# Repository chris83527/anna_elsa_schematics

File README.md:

# Schematics for Anna & Elsa fruit machine project
## based on ESP32 microcontroller

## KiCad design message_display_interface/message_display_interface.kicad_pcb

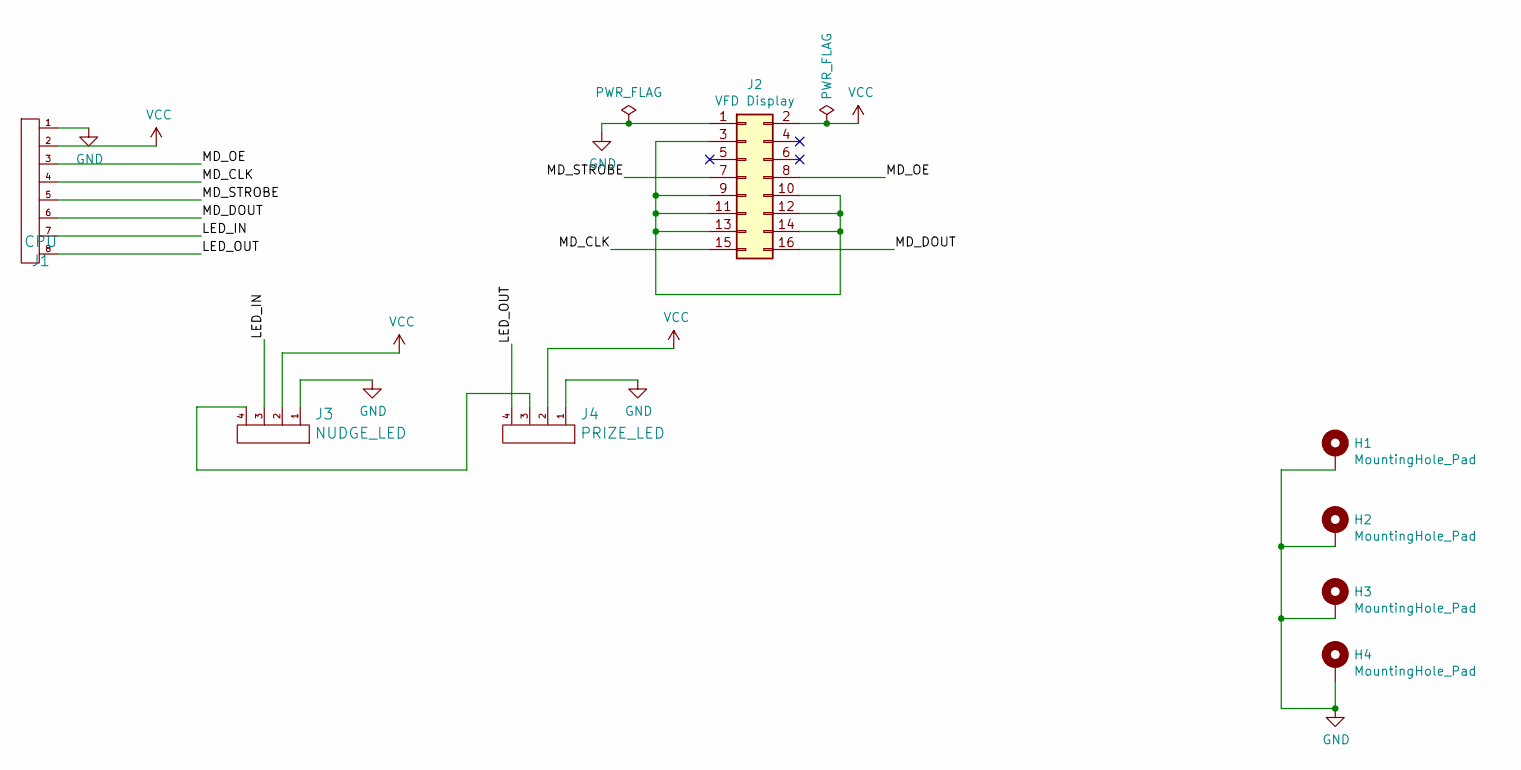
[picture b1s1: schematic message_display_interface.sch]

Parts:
H1, H2, H3, H4: MountingHole_Pad; MountingHole_3.2mm_M3_Pad
J1: CPU; JST_XH_B8B-XH-A_1x08_P2.50mm_Vertical
J2: VFD Display; IDC-Header_2x08_P2.54mm_Vertical
J3: NUDGE_LED; JST_XH_B4B-XH-A_1x04_P2.50mm_Vertical
J4: PRIZE_LED; JST_XH_B4B-XH-A_1x04_P2.50mm_Vertical

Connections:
/LED_IN: J1.7, J3.3
/LED_OUT: J1.8, J4.4
/MD_CLK: J1.4, J2.15
/MD_DOUT: J1.6, J2.16
/MD_OE: J1.3, J2.8
/MD_STROBE: J1.5, J2.7
GND: H1.1, H2.1, H3.1, H4.1, J1.1, J2.1, J3.1, J4.1
unnamed: J2.3, J2.9, J2.10, J2.11, J2.12, J2.13, J2.14
unnamed: J3.4, J4.3
VCC: J1.2, J2.2, J3.2, J4.2

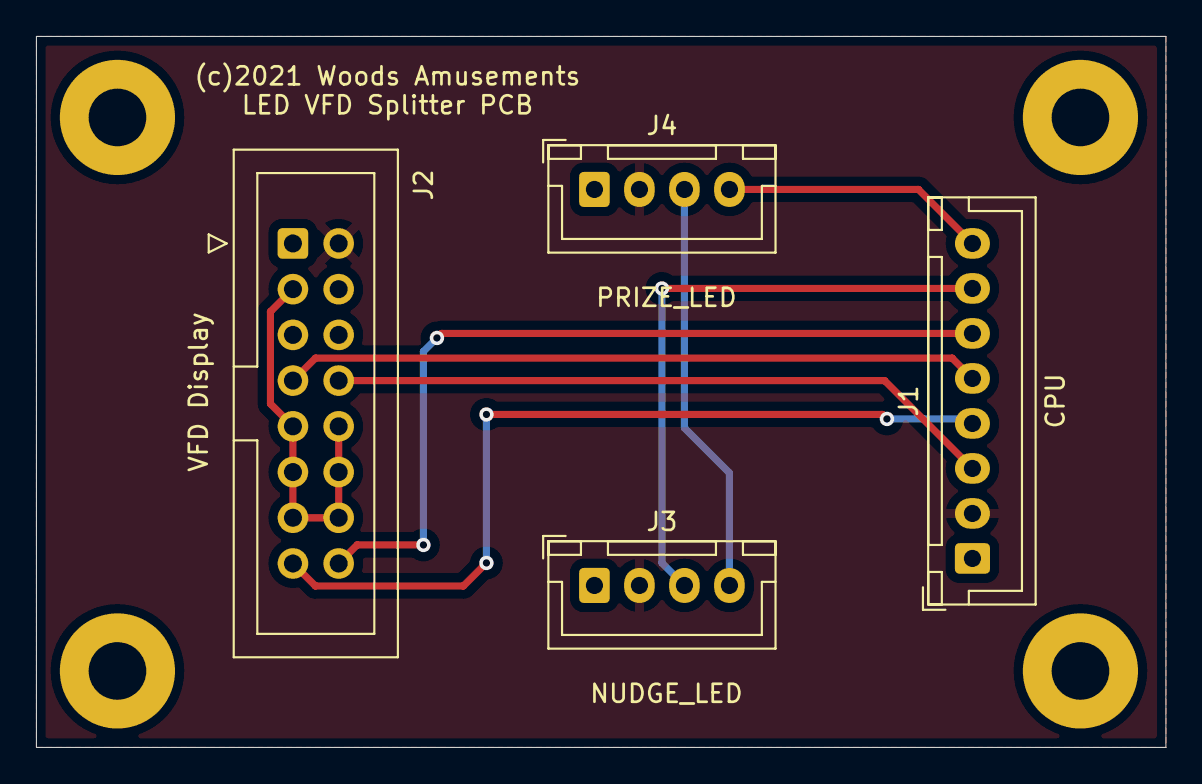
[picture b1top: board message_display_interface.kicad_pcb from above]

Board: 2 copper layers, 62.8 x 39.5 mm, 8 parts (0 on the bottom side), 10 nets.

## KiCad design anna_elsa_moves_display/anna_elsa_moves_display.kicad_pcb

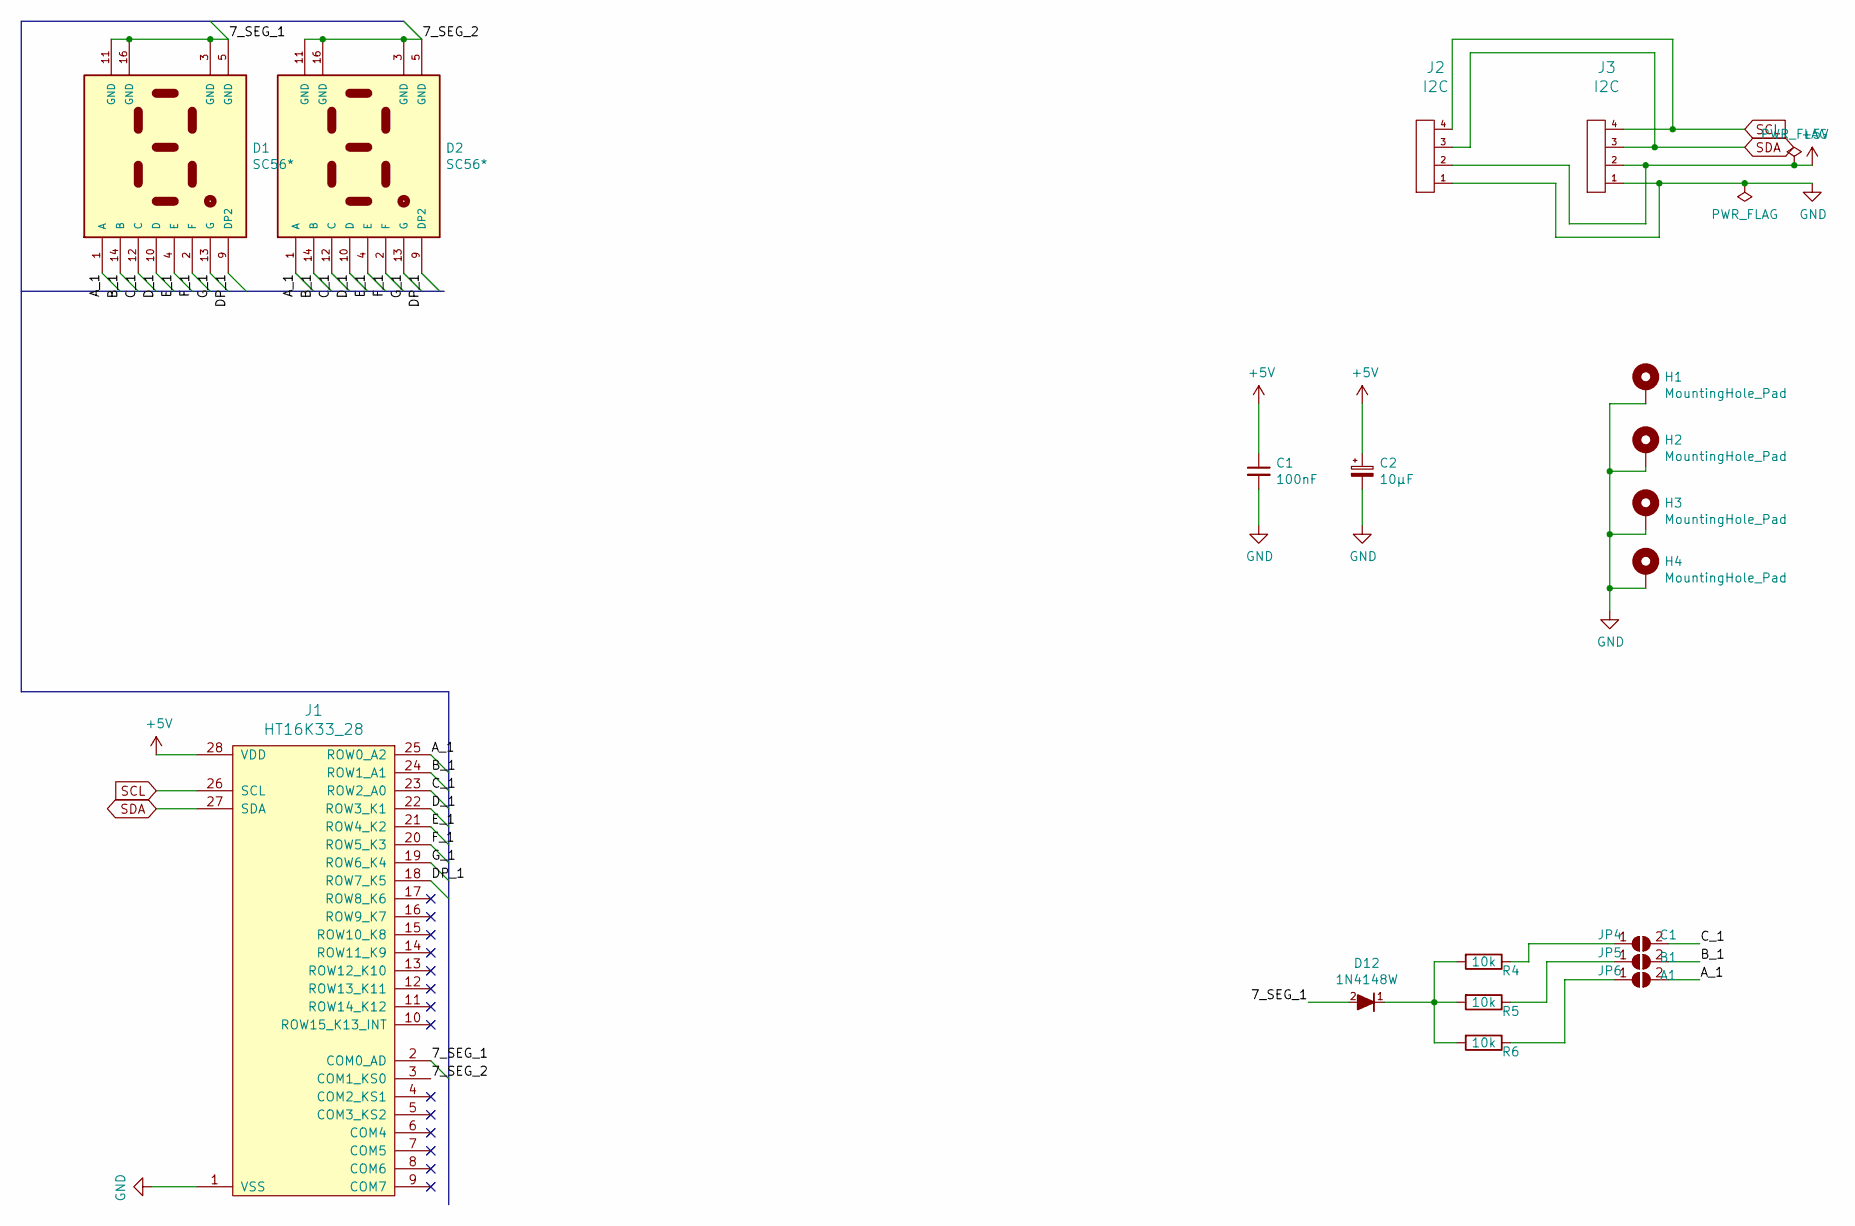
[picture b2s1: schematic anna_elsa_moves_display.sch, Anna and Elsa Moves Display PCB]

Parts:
C1: 100nF; C_Disc_D4.3mm_W1.9mm_P5.00mm; LCSC C14663
C2: 10µF; CP_Radial_D6.3mm_P2.50mm; LCSC C96123
D1, D2: SC56*; DIP14_KINGBRIGHT_SX08
D12: 1N4148W; D_A-405_P7.62mm_Horizontal; LCSC C81598
H1, H2, H3, H4: MountingHole_Pad; MountingHole_3.2mm_M3_Pad
J1: HT16K33_28; SOP-28_7.5x15.4mm_P1.27mm
J2, J3: I2C; JST_XH_B4B-XH-A_1x04_P2.50mm_Vertical
JP4: C1; SolderJumper-2_P1.3mm_Open_Pad1.0x1.5mm
JP5: B1; SolderJumper-2_P1.3mm_Open_Pad1.0x1.5mm
JP6: A1; SolderJumper-2_P1.3mm_Open_Pad1.0x1.5mm
R4, R6: 10k; R_Axial_DIN0207_L6.3mm_D2.5mm_P7.62mm_Horizontal; LCSC C25804
R5: 10k; R_Axial_DIN0207_L6.3mm_D2.5mm_P7.62mm_Horizontal

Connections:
+5V: C1.1, C2.1, J1.28 (VDD), J2.2, J3.2
/7_SEG_1: D1.3 (GND), D1.5 (GND), D1.11 (GND), D1.16 (GND), D12.2 (A), J1.2 (COM0_AD)
/7_SEG_2: D2.3 (GND), D2.5 (GND), D2.11 (GND), D2.16 (GND), J1.3 (COM1_KS0)
/A_1: D1.1 (A), D2.1 (A), J1.25 (ROW0_A2), JP6.2 (B)
/B_1: D1.14 (B), D2.14 (B), J1.24 (ROW1_A1), JP5.2 (B)
/C_1: D1.12 (C), D2.12 (C), J1.23 (ROW2_A0), JP4.2 (B)
/DP_1: D1.9 (DP2), D2.9 (DP2), J1.18 (ROW7_K5)
/D_1: D1.10 (D), D2.10 (D), J1.22 (ROW3_K1)
/E_1: D1.4 (E), D2.4 (E), J1.21 (ROW4_K2)
/F_1: D1.2 (F), D2.2 (F), J1.20 (ROW5_K3)
/G_1: D1.13 (G), D2.13 (G), J1.19 (ROW6_K4)
GND: C1.2, C2.2, H1.1, H2.1, H3.1, H4.1, J1.1 (VSS), J2.1, J3.1
unnamed: D12.1 (K), R4.2, R5.2, R6.2
unnamed: JP4.1 (A), R4.1
unnamed: JP5.1 (A), R5.1
unnamed: JP6.1 (A), R6.1
SCL: J1.26 (SCL), J2.4, J3.4
SDA: J1.27 (SDA), J2.3, J3.3

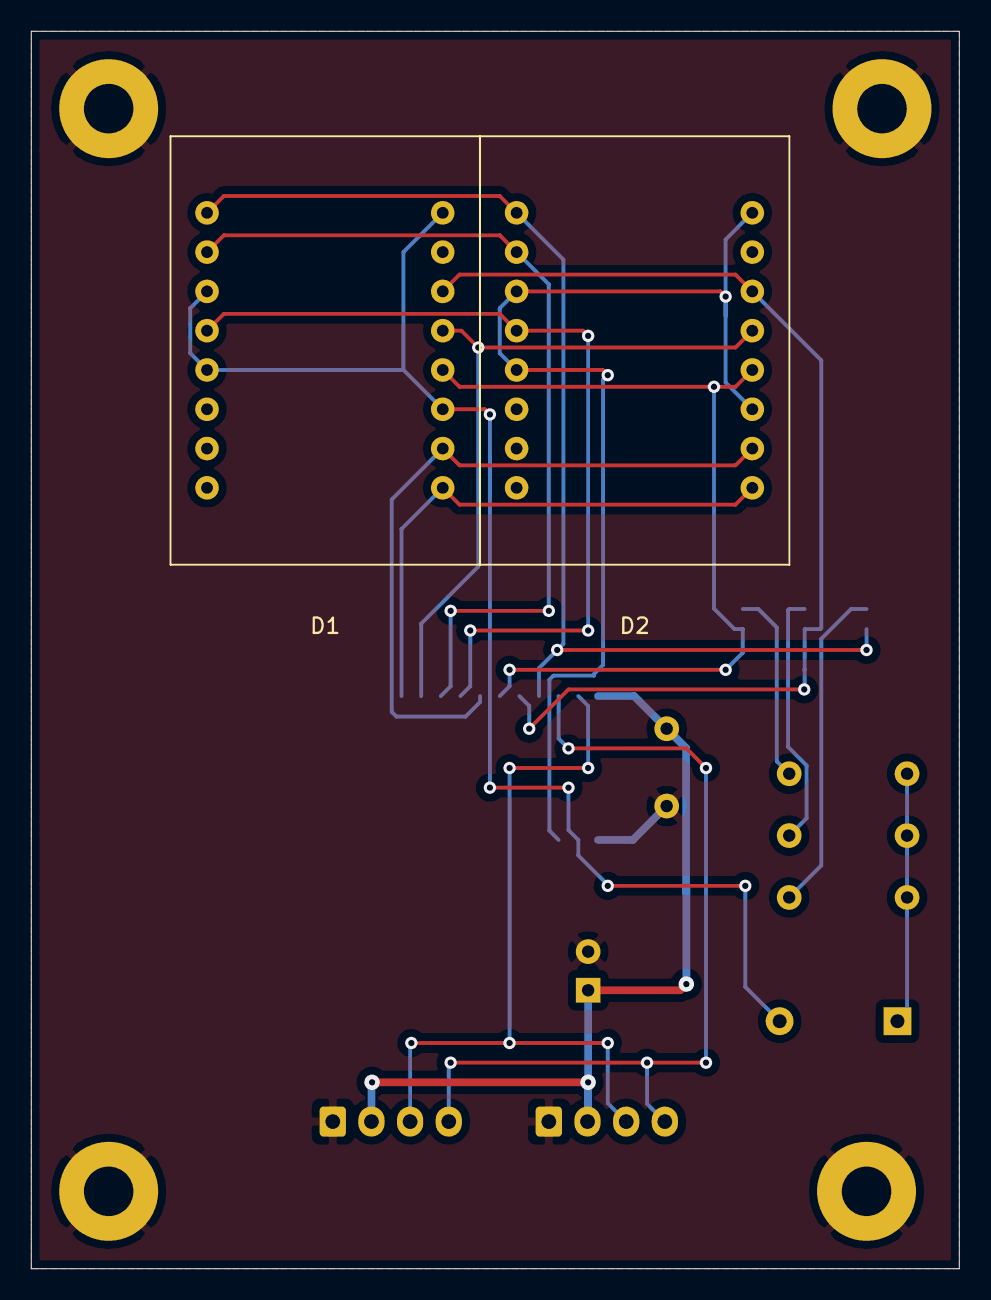
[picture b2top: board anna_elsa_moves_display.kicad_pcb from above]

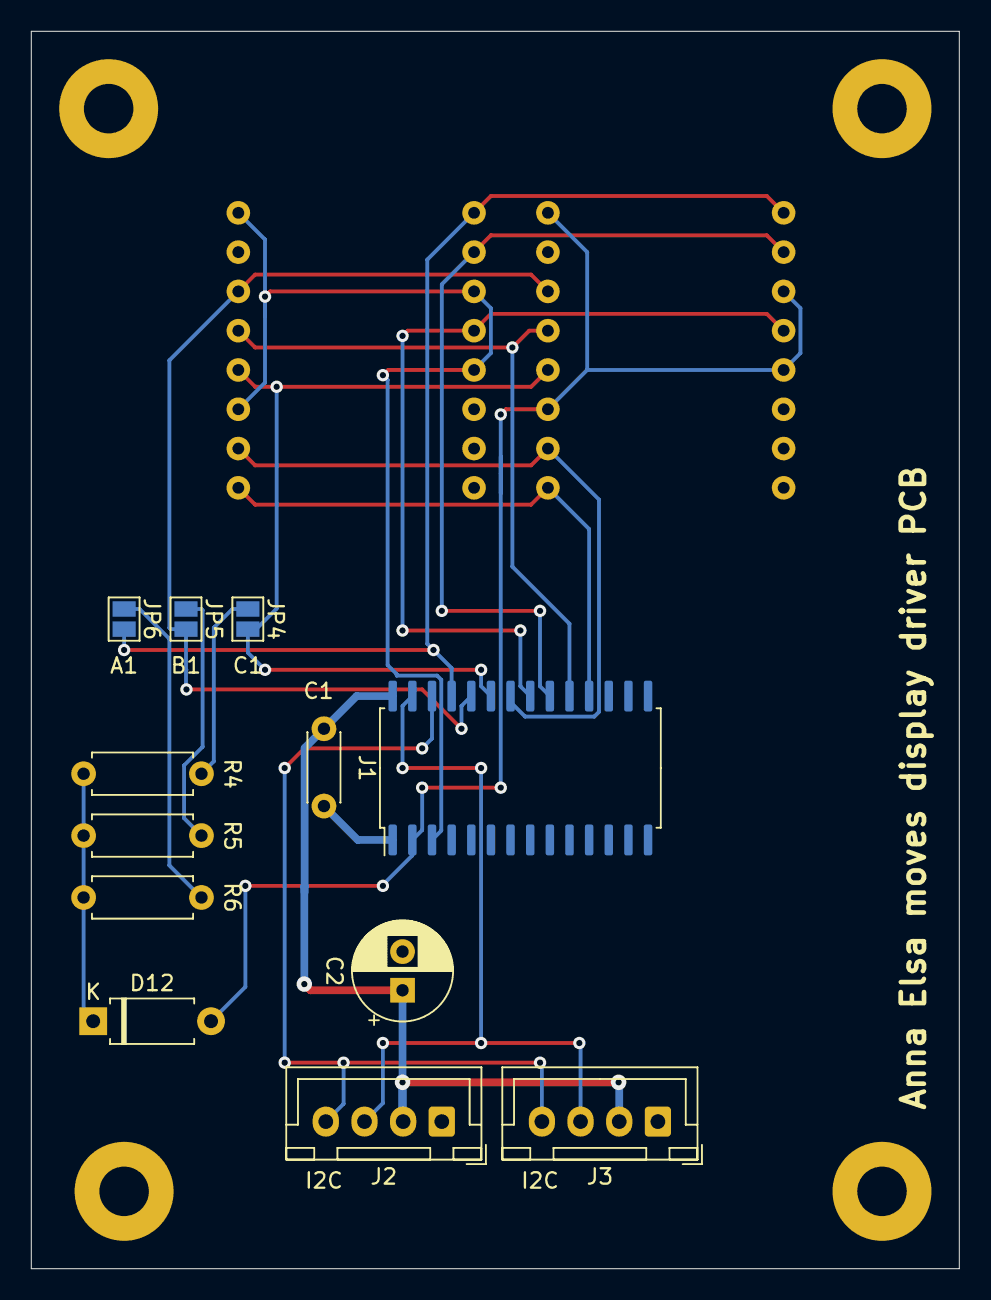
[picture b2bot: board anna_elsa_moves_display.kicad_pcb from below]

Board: 2 copper layers, 60.0 x 80.0 mm, 18 parts (12 on the bottom side), 18 nets.

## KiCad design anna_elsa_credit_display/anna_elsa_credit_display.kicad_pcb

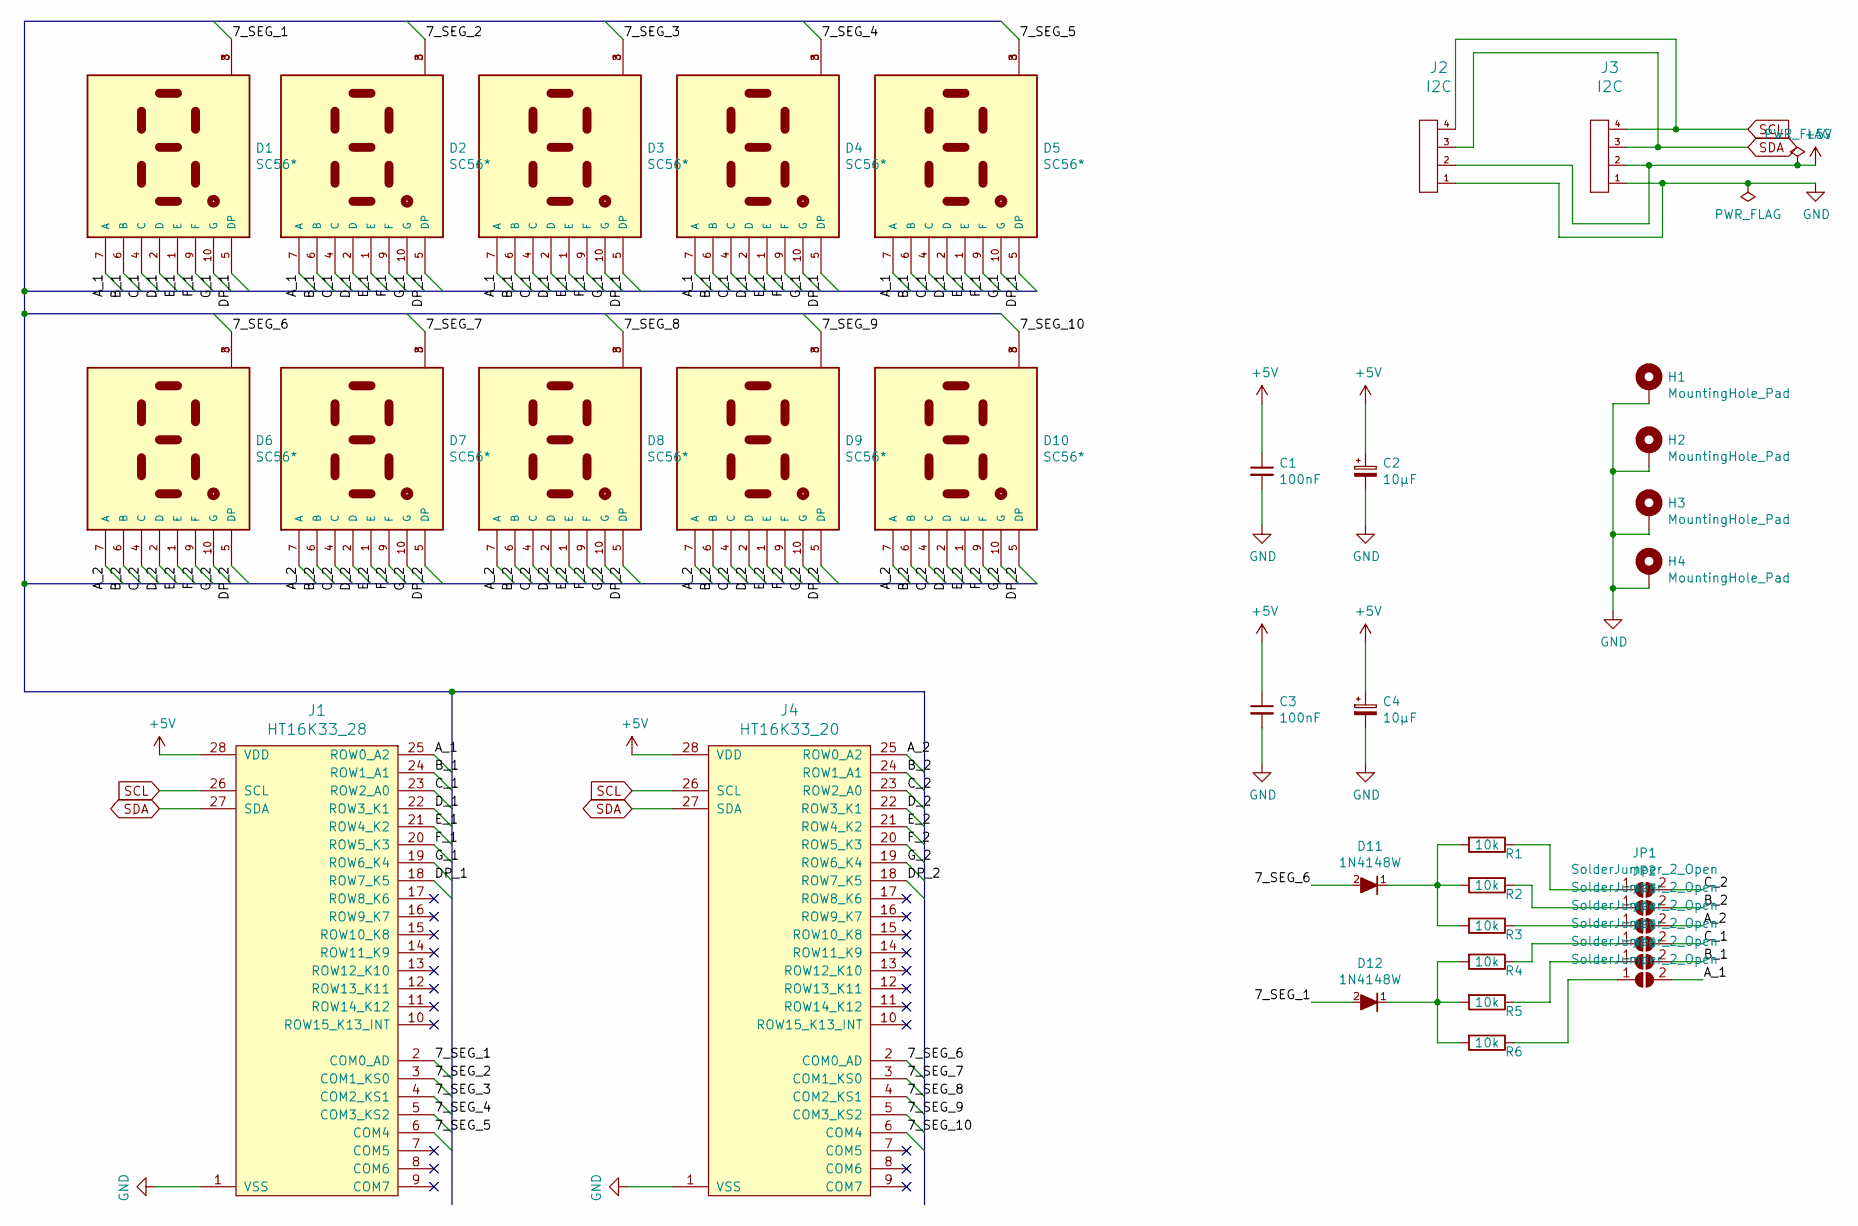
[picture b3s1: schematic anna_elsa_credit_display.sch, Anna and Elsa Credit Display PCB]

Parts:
C1, C3: 100nF; C_Disc_D4.3mm_W1.9mm_P5.00mm; LCSC C14663
C2, C4: 10µF; CP_Radial_D6.3mm_P2.50mm; LCSC C96123
D1, D2, D3, D4, D5, D6, D7, D8, D9, D10: SC56*; DIP10_KINGBRIGHT_SX56
D11, D12: 1N4148W; D_A-405_P7.62mm_Horizontal; LCSC C81598
H1, H2, H3, H4: MountingHole_Pad; MountingHole_3.2mm_M3_Pad
J1: HT16K33_28; SOP-28_7.5x15.4mm_P1.27mm
J2, J3: I2C; JST_XH_B4B-XH-A_1x04_P2.50mm_Vertical
J4: HT16K33_20; SOP-28_7.5x15.4mm_P1.27mm
JP1, JP2, JP3, JP4, JP5, JP6: SolderJumper_2_Open; SolderJumper-2_P1.3mm_Open_Pad1.0x1.5mm
R1, R2, R4, R6: 10k; R_Axial_DIN0207_L6.3mm_D2.5mm_P7.62mm_Horizontal; LCSC C25804
R3, R5: 10k; R_Axial_DIN0207_L6.3mm_D2.5mm_P7.62mm_Horizontal

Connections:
+5V: C1.1, C2.1, C3.1, C4.1, J1.28 (VDD), J2.2, J3.2, J4.28 (VDD)
/7_SEG_1: D1.3, D1.8, D12.2 (A), J1.2 (COM0_AD)
/7_SEG_2: D2.3, D2.8, J1.3 (COM1_KS0)
/7_SEG_3: D3.3, D3.8, J1.4 (COM2_KS1)
/7_SEG_4: D4.3, D4.8, J1.5 (COM3_KS2)
/7_SEG_5: D5.3, D5.8, J1.6 (COM4)
/7_SEG_6: D6.3, D6.8, D11.2 (A), J4.2 (COM0_AD)
/7_SEG_7: D7.3, D7.8, J4.3 (COM1_KS0)
/7_SEG_8: D8.3, D8.8, J4.4 (COM2_KS1)
/7_SEG_9: D9.3, D9.8, J4.5 (COM3_KS2)
/7_SEG_10: D10.3, D10.8, J4.6 (COM4)
/A_1: D1.7 (A), D2.7 (A), D3.7 (A), D4.7 (A), D5.7 (A), J1.25 (ROW0_A2), JP6.2 (B)
/A_2: D6.7 (A), D7.7 (A), D8.7 (A), D9.7 (A), D10.7 (A), J4.25 (ROW0_A2), JP3.2 (B)
/B_1: D1.6 (B), D2.6 (B), D3.6 (B), D4.6 (B), D5.6 (B), J1.24 (ROW1_A1), JP5.2 (B)
/B_2: D6.6 (B), D7.6 (B), D8.6 (B), D9.6 (B), D10.6 (B), J4.24 (ROW1_A1), JP2.2 (B)
/C_1: D1.4 (C), D2.4 (C), D3.4 (C), D4.4 (C), D5.4 (C), J1.23 (ROW2_A0), JP4.2 (B)
/C_2: D6.4 (C), D7.4 (C), D8.4 (C), D9.4 (C), D10.4 (C), J4.23 (ROW2_A0), JP1.2 (B)
/DP_1: D1.5 (DP), D2.5 (DP), D3.5 (DP), D4.5 (DP), D5.5 (DP), J1.18 (ROW7_K5)
/DP_2: D6.5 (DP), D7.5 (DP), D8.5 (DP), D9.5 (DP), D10.5 (DP), J4.18 (ROW7_K5)
/D_1: D1.2 (D), D2.2 (D), D3.2 (D), D4.2 (D), D5.2 (D), J1.22 (ROW3_K1)
/D_2: D6.2 (D), D7.2 (D), D8.2 (D), D9.2 (D), D10.2 (D), J4.22 (ROW3_K1)
/E_1: D1.1 (E), D2.1 (E), D3.1 (E), D4.1 (E), D5.1 (E), J1.21 (ROW4_K2)
/E_2: D6.1 (E), D7.1 (E), D8.1 (E), D9.1 (E), D10.1 (E), J4.21 (ROW4_K2)
/F_1: D1.9 (F), D2.9 (F), D3.9 (F), D4.9 (F), D5.9 (F), J1.20 (ROW5_K3)
/F_2: D6.9 (F), D7.9 (F), D8.9 (F), D9.9 (F), D10.9 (F), J4.20 (ROW5_K3)
/G_1: D1.10 (G), D2.10 (G), D3.10 (G), D4.10 (G), D5.10 (G), J1.19 (ROW6_K4)
/G_2: D6.10 (G), D7.10 (G), D8.10 (G), D9.10 (G), D10.10 (G), J4.19 (ROW6_K4)
GND: C1.2, C2.2, C3.2, C4.2, H1.1, H2.1, H3.1, H4.1, J1.1 (VSS), J2.1, J3.1, J4.1 (VSS)
unnamed: D11.1 (K), R1.2, R2.2, R3.2
unnamed: D12.1 (K), R4.2, R5.2, R6.2
unnamed: JP1.1 (A), R1.1
unnamed: JP2.1 (A), R2.1
unnamed: JP3.1 (A), R3.1
unnamed: JP4.1 (A), R4.1
unnamed: JP5.1 (A), R5.1
unnamed: JP6.1 (A), R6.1
SCL: J1.26 (SCL), J2.4, J3.4, J4.26 (SCL)
SDA: J1.27 (SDA), J2.3, J3.3, J4.27 (SDA)

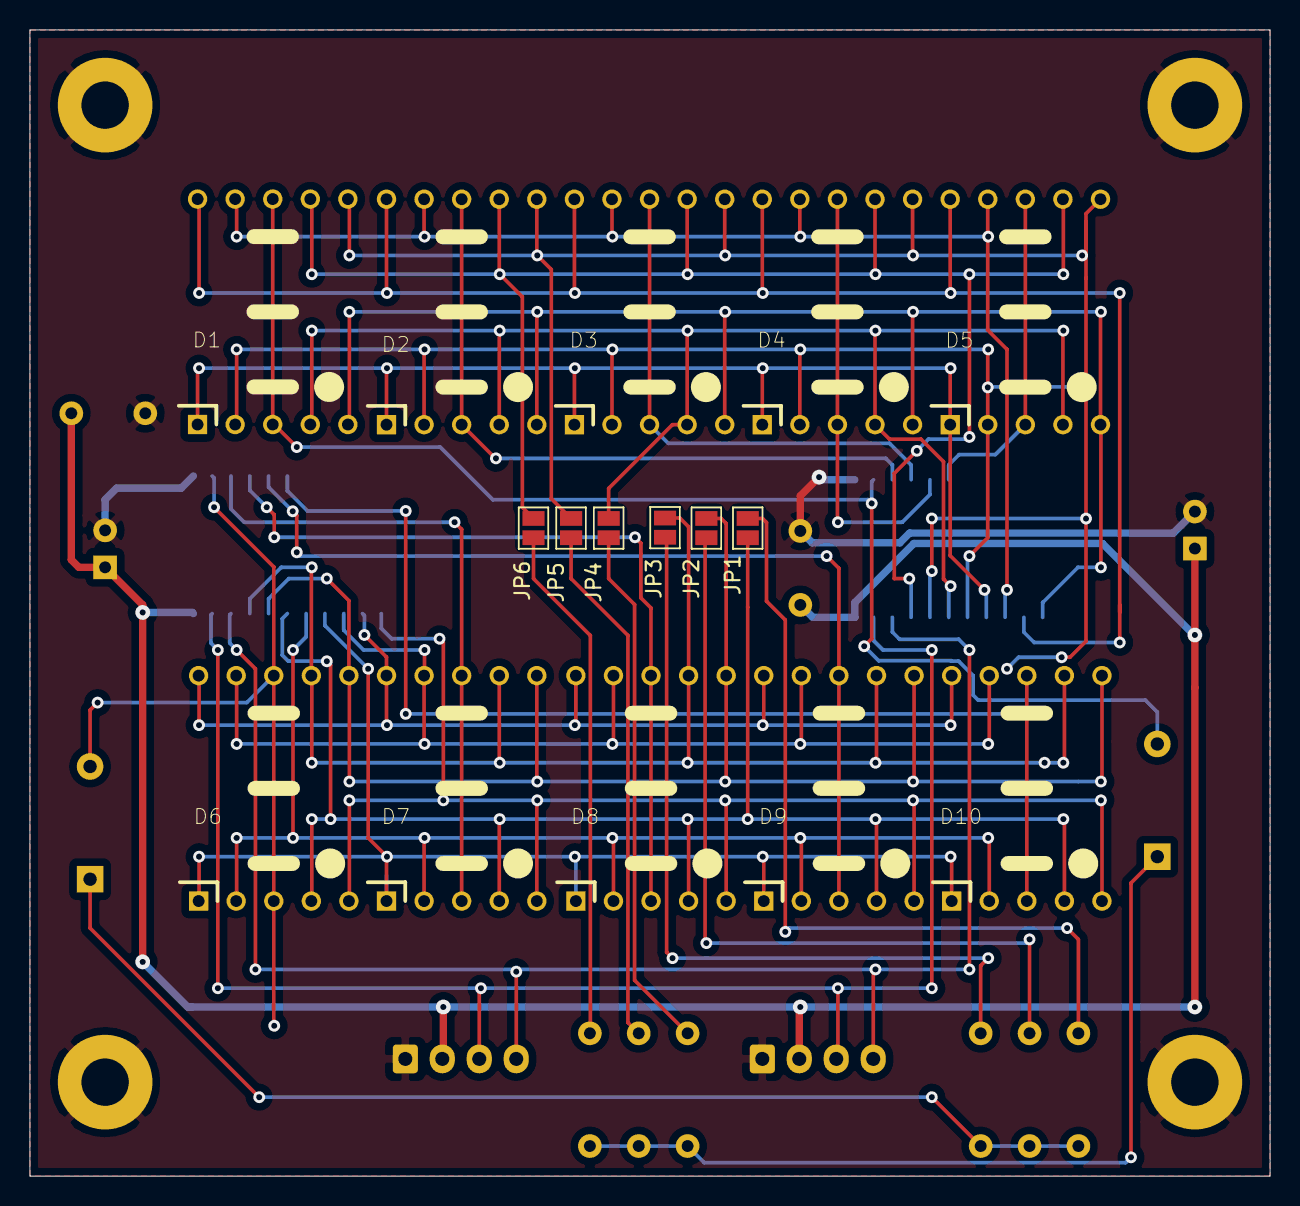
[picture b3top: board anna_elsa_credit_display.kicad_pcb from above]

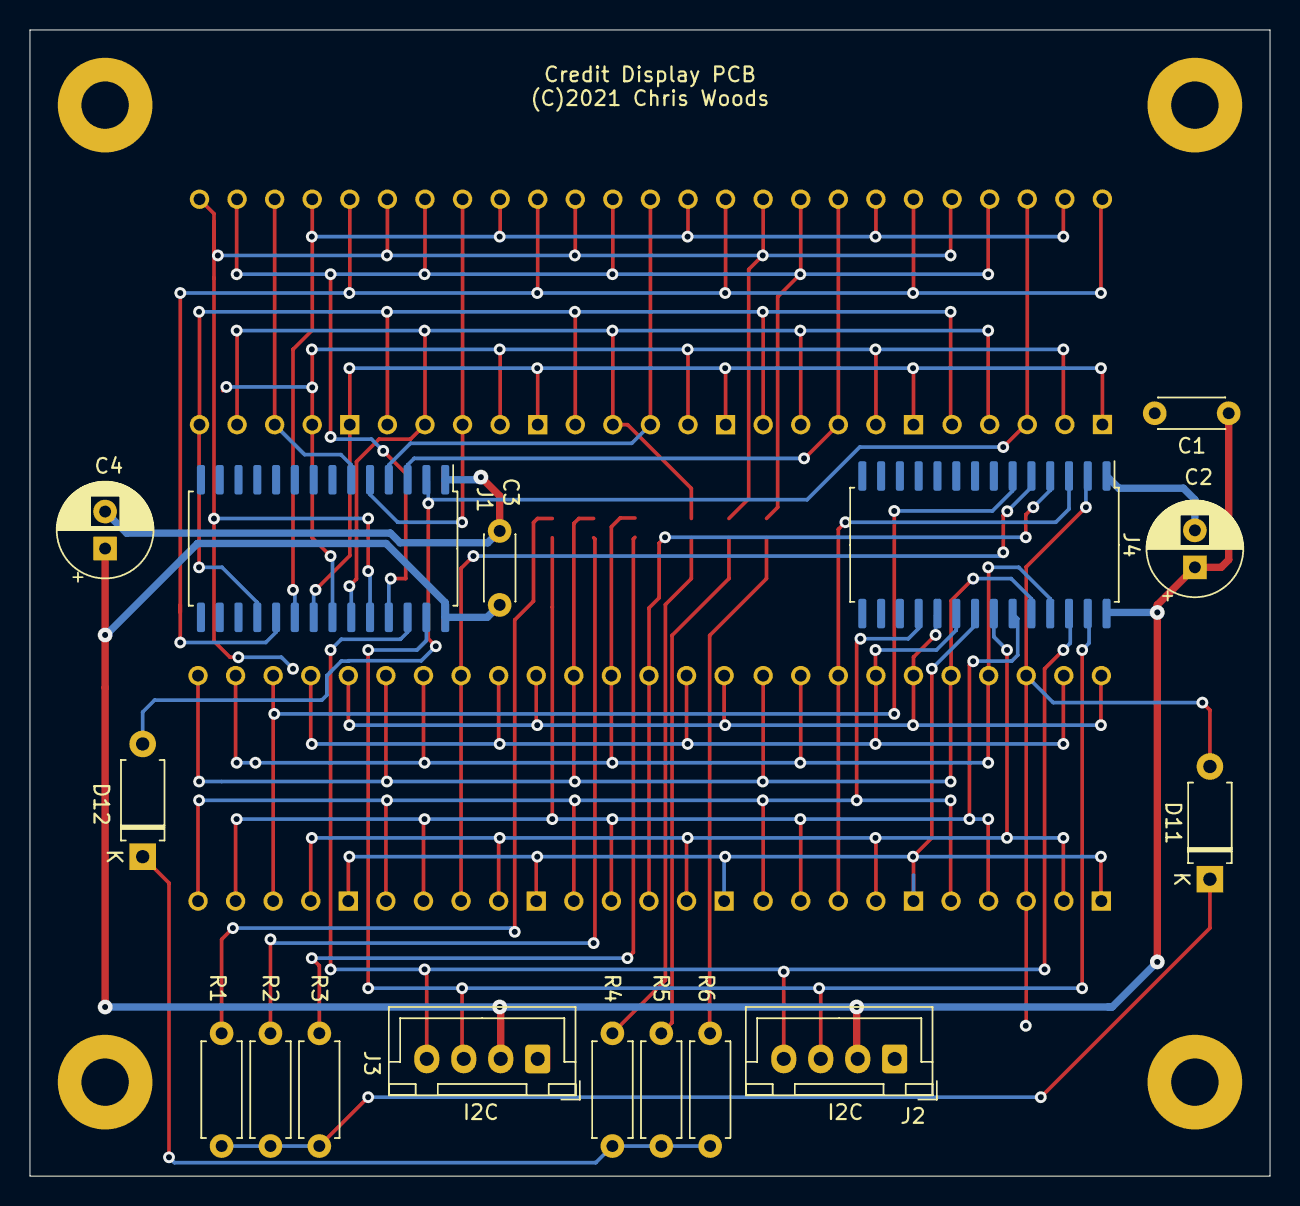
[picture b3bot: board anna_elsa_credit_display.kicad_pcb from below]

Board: 2 copper layers, 83.8 x 77.5 mm, 36 parts (16 on the bottom side), 38 nets.

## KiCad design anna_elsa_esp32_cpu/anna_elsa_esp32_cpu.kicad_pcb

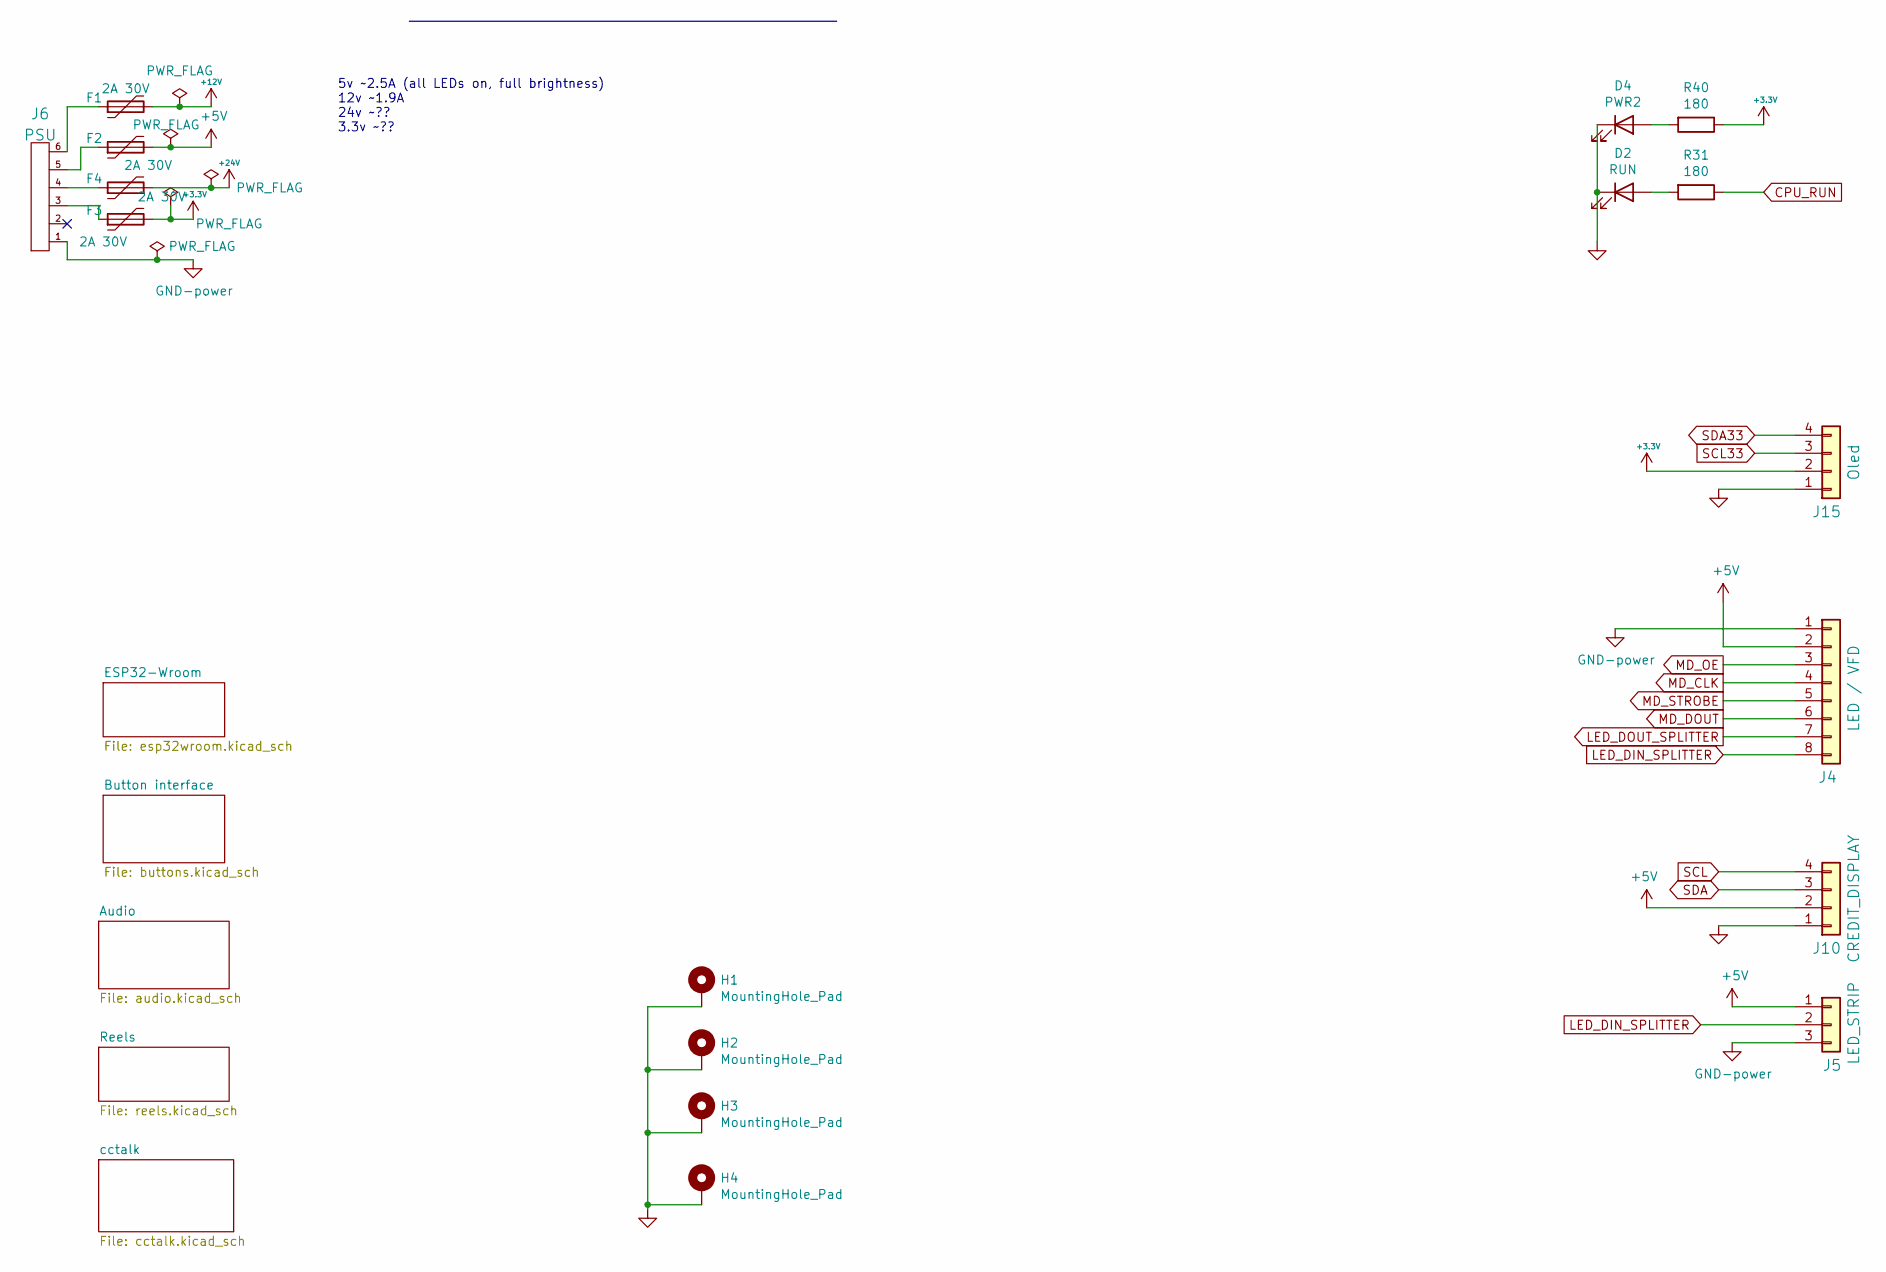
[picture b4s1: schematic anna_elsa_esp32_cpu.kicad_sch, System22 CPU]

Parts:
D2: RUN; LED_0805_2012Metric; MPN NCD0805R1; LCSC C84256
D4: PWR2; LED_0805_2012Metric; MPN NCD0805R1; LCSC C84256
F1, F2, F3, F4: 2A 30V; Fuse_1812_4532Metric; MPN BSMD1812-200-30V; LCSC C960026
H1, H2, H3, H4: MountingHole_Pad; MountingHole_3.2mm_M3_Pad_Via
J4: LED / VFD; JST_XH_B8B-XH-A_1x08_P2.50mm_Vertical
J5: LED_STRIP; JST_XH_B3B-XH-A_1x03_P2.50mm_Vertical
J6: PSU; PhoenixContact_MCV_1,5_6-G-3.5_1x06_P3.50mm_Vertical
J10: CREDIT_DISPLAY; JST_XH_B4B-XH-A_1x04_P2.50mm_Vertical
J15: Oled; PinSocket_1x04_P2.54mm_Vertical
R31, R40: 180; R_0805_2012Metric; MPN 0805W8F1800T5E; LCSC C25270

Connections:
+3.3V: F3.2, J15.2, R40.1; also elsewhere on the board
+5V: F2.2, J4.2, J5.1, J10.2; also elsewhere on the board
+12V: F1.2; also elsewhere on the board
+24V: F4.2; also elsewhere on the board
CPU_RUN: R31.1; also elsewhere on the board
LED_DIN_SPLITTER: J4.8, J5.2
LED_DOUT_SPLITTER: J4.7; also elsewhere on the board
MD_CLK: J4.4; also elsewhere on the board
MD_DOUT: J4.6; also elsewhere on the board
MD_OE: J4.3; also elsewhere on the board
MD_STROBE: J4.5; also elsewhere on the board
unnamed: D2.2 (A), R31.2
unnamed: D4.2 (A), R40.2
unnamed: F1.1, J6.6
unnamed: F2.1, J6.5
unnamed: F3.1, J6.3
unnamed: F4.1, J6.4
SCL: J10.4; also elsewhere on the board
SCL33: J15.3; also elsewhere on the board
SDA: J10.3; also elsewhere on the board
SDA33: J15.4; also elsewhere on the board

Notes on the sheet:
5v ~2.5A (all LEDs on, full brightness) 12v ~1.9A 24v ~?? 3.3v ~??

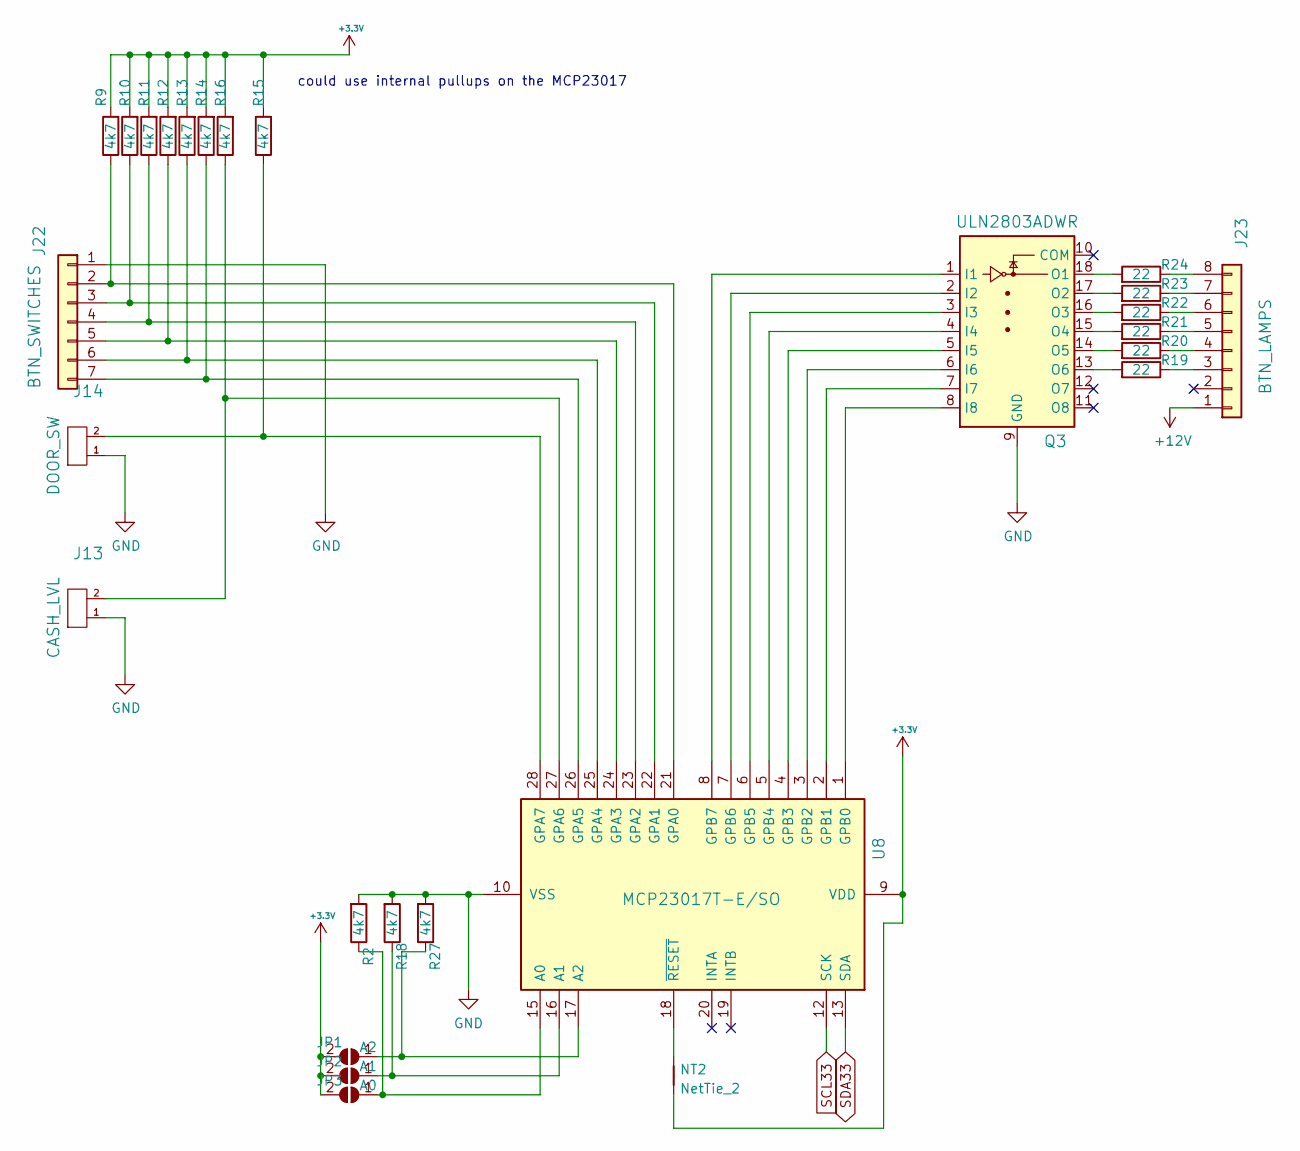
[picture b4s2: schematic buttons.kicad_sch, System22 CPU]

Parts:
J13: CASH_LVL; JST_XH_B2B-XH-A_1x02_P2.50mm_Vertical
J14: DOOR_SW; JST_XH_B2B-XH-A_1x02_P2.50mm_Vertical
J22: BTN_SWITCHES; JST_XH_B7B-XH-A_1x07_P2.50mm_Vertical
J23: BTN_LAMPS; JST_XH_B8B-XH-A_1x08_P2.50mm_Vertical
JP1: A2; SolderJumper-2_P1.3mm_Open_RoundedPad1.0x1.5mm
JP2: A1; SolderJumper-2_P1.3mm_Open_RoundedPad1.0x1.5mm
JP3: A0; SolderJumper-2_P1.3mm_Open_RoundedPad1.0x1.5mm
NT2: NetTie_2; NetTie-2_SMD_Pad0.5mm
Q3: ULN2803ADWR; SOIC-18W_7.5x11.6mm_P1.27mm; MPN ULN2803ADWR; Digi-Key_PN 296-15777-1-ND
R2, R9, R10, R11, R12, R13, R14, R15, R16, R18, R27: 4k7; R_0805_2012Metric; LCSC C17673
R19, R20, R21, R22, R23, R24: 22; R_0805_2012Metric; LCSC C17561
U8: MCP23017T-E/SO; SOIC-28W_7.5x17.9mm_P1.27mm; MPN MCP23017-E/SO; Digi-Key_PN MCP23017-E/SO-ND

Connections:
+3.3V: JP1.2 (B), JP2.2 (B), JP3.2 (B), NT2.1, R9.2, R10.2, R11.2, R12.2, R13.2, R14.2, R15.2, R16.2, U8.9 (VDD); also elsewhere on the board
+12V: J23.1; also elsewhere on the board
unnamed: J13.2, R16.1, U8.27 (GPA6)
unnamed: J14.2, R15.1, U8.28 (GPA7)
unnamed: J22.2, R9.1, U8.21 (GPA0)
unnamed: J22.3, R10.1, U8.22 (GPA1)
unnamed: J22.4, R11.1, U8.23 (GPA2)
unnamed: J22.5, R12.1, U8.24 (GPA3)
unnamed: J22.6, R13.1, U8.25 (GPA4)
unnamed: J22.7, R14.1, U8.26 (GPA5)
unnamed: J23.3, R19.1
unnamed: J23.4, R20.1
unnamed: J23.5, R21.1
unnamed: J23.6, R22.1
unnamed: J23.7, R23.1
unnamed: J23.8, R24.1
unnamed: JP1.1 (A), R27.1, U8.17 (A2)
unnamed: JP2.1 (A), R18.1, U8.16 (A1)
unnamed: JP3.1 (A), R2.1, U8.15 (A0)
unnamed: NT2.2, U8.18 (~RESET)
unnamed: Q3.1 (I1), U8.8 (GPB7)
unnamed: Q3.2 (I2), U8.7 (GPB6)
unnamed: Q3.3 (I3), U8.6 (GPB5)
unnamed: Q3.4 (I4), U8.5 (GPB4)
unnamed: Q3.5 (I5), U8.4 (GPB3)
unnamed: Q3.6 (I6), U8.3 (GPB2)
unnamed: Q3.7 (I7), U8.2 (GPB1)
unnamed: Q3.8 (I8), U8.1 (GPB0)
unnamed: Q3.13 (O6), R19.2
unnamed: Q3.14 (O5), R20.2
unnamed: Q3.15 (O4), R21.2
unnamed: Q3.16 (O3), R22.2
unnamed: Q3.17 (O2), R23.2
unnamed: Q3.18 (O1), R24.2
SCL33: U8.12 (SCK); also elsewhere on the board
SDA33: U8.13 (SDA); also elsewhere on the board

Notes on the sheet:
could use internal pullups on the MCP23017

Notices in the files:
anna_elsa_credit_display/anna_elsa_credit_display.kicad_pcb:
(C)2021 Chris Woods
anna_elsa_esp32_cpu/anna_elsa_esp32_cpu.kicad_pcb:
©2022 Chris Woods
message_display_interface/message_display_interface.kicad_pcb:
(c)2021 Woods Amusements
